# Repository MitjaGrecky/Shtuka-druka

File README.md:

# Shtuka Druka

An open, standalone desktop music instrument: synthesizer, sampler and DAW in one box.
The idea is improvising with sound from everywhere: capture audio from any source,
then shape it with filters and effects.

Status: design phase. Panel layout v7, enclosure, I/O, audio chain and compute platform are decided.
First board: M1 screen knobs module (being routed). Next: W1 Levels, then a 1:1 cardboard mockup.

## What is here

| Folder | Contents |
|---|---|
| `docs/ru/` | Research and design documents (Russian). Start with `README.md` (map of documents) and `decisions/README.md` — the single source of truth for every decision, split by topic |
| `bench/` | CPU benchmark: how many reference tracks a processor can run at 48 kHz / 128 samples |
| `mockup/` | 1:1 cardboard mockup templates (A4, PDF) and the script that generates them |
| `model3d/` | Interactive 3D model of panel v7, built from `mockup/layout/layout_v7.json` (open `index.html` in a browser; rebuild with `build_model3d_v7.py`) |
| `firmware/protocol/` | Board <-> computer protocol (SDP v0): C header for firmware and host |
| `tools/` | `sdp.py`: reference codec, self-test and frame monitor |
| `hardware/` | KiCad boards, generated from Python (`gen/`), checked by CI: `m1-screen-knobs` (first board), `w1-levels` |
| `notes/handoff.md` | Task queue between the cloud and local Claude sessions (rules in `CLAUDE.md`) |
| `.github/workflows/` | CI: ERC, DRC with schematic parity, BOM, Gerbers for every board on every push |

## Key facts

- 8x8 RGB pad grid, 16+ tracks (target 32-64), endless encoders with LED rings, 10.1" screen at 30 deg
- Body 515 x 460 mm, 68 mm high at the front, 143 mm at the rear, 30 deg slope for the screen, detachable wrist rest
- Inputs: 2 combo XLR/TRS, 2 Hi-Z, phono with RIAA, 8 line inputs, USB audio, 2-4 CV
- Converters: Cirrus Logic Pro (CS5308P/CS5304P ADC, CS4308P DAC), two-path inputs without a preamp chip
- Outputs: Main and Aux (balanced TRS), RCA copy of Main, 2 headphones
- MIDI: 2 in / 4 out DIN, 1 in / 2 out TRS (type A/B switchable); 8 CV/Gate, sync block, Ableton Link
- Compute: x86 on a Mini-ITX board (Intel N100 to start, 8-core upgrade on the same mounts)
- Two RP2350 boards (panel, control) over internal USB; audio board on two xcore.ai, USB Audio Class 2

## Licenses

- Software: GNU AGPL-3.0-or-later (`LICENSE`)
- Hardware: CERN-OHL-S-2.0 (`hardware/LICENSE`)

---

Штука Дрюка — открытый настольный инструмент: синтезатор, сэмплер и DAW в одном корпусе.
Документы проекта на русском лежат в `docs/ru/`, карта документов — `docs/ru/README.md`, все решения — в `docs/ru/decisions/` (начинать с `README.md`).

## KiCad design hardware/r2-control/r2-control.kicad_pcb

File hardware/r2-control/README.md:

# R2 - Control board (rear wall, right part)

The RP2350 of the control board (R85) with everything that is not audio at the rear wall: MIDI, CV/Gate, sync, the internal
USB hub and the control lines to the audio boards. DIN, USB, LAN and DC are panel parts on nuts with cables (R141).
Research and decisions: `docs/ru/34_rear_boards_research.md`, R118, R135-R143. Map of boards: `docs/ru/29_board_map.md`.

**Status: rev 0.6 - schematic and placed board, not routed** (234 parts, 4 layers; 14.11.2026; rev 0.5 = ATT1/ATT2 and the 74HC595, task #25; rev 0.6 = 7 x M3 mounting holes). Rear wall = the 3D model
of panel v7 (R142). MIDI DIN, USB, LAN and DC are panel parts on nuts with short cables (R141, the shelf R2b of rev 0.3 is
dropped): R2 carries the twenty 3.5 mm jacks and six JST PH headers for the DIN cables. Outline: the Control block, rear
x 88-263, z 10-113, without the window behind the DIN sockets (rear x 88-156, z 38-113) - an L, 175 x 103 mm.

| Block | Parts | Notes |
|---|---|---|
| MCU | RP2350A (C42411118), W25Q128JVSIQ (C97521, 16 MB QSPI), 12 MHz ABM8-272-T3 (C20625731), core regulator with 3.3 uH AOTA-B201610S3R3 (C42411119), BOOTSEL button | As Raspberry Pi's minimal design (Hardware design with RP2350) |
| USB hub | USB2514B (C220679), 24 MHz X322524MOB4SI (C70590) | Up: Mini-ITX USB header. Down: 1 RP2350, 2 panel P2 (R86), 3 A1 port A (R82), 4 spare. Straps low by the internal pull-downs = default configuration |
| MIDI DIN | 2 in (TLP2361 at 3.3 V), 4 out; sockets on the wall, one cable each to a JST PH header (out: 3 pins 4, 5, shield; in: 2 pins 4, 5) | CA-033 3.3 V: 33 R 0.5 W + 10 R per output; every output has its own port (R34). Any MIDI output (DIN 1-4, TRS O1/O2) can be **Thru** from In 1 or In 2, set in the menu: the RP2350 PIO copies the input bit by bit (microseconds, no CPU); no Thru labels on the panel, R144 |
| MIDI TRS | 1 in, 2 out: stereo Hroparts PJ-3920-3A (C707259, R143) | Out: tip and ring each from a GPIO through 22 R - type A/B is swapped in firmware (R32). In: two optos back to back, type A and B both work |
| CV/Gate out 1-8 | 2 x DAC80504RTET (C2862796; internal 2.5 V ref divided by 2, gain 2 = 0-2.5 V), 3 x OPA4197 (C2057327) on +-12 V | Vout = 8.06 (Vdac - 1.25 V) = -10.1 ... +10.1 V around a buffered REF/2; reset to mid-scale = 0 V; 1k output resistors. Step 0.31 mV = 0.37 cent at 1 V/oct |
| CV in 1-4 | RP2350 ADC0-3 | -10 ... +10 V -> 0 ... 3.03 V (100k / 33k to 3.3 V / 39k to GND), BAT54S clamp |
| Sync | 3 out, 2 in | Out: GPIO -> op-amp x1.51 -> 0 / +5 V. In: NPN inverter, 22k / 100k, negative clamp |
| To A1/R1 (2x7) | PH48_1, PH48_2, PHONO, MUTE, R2_OK, ATT1, ATT2 (pins 1, 3, 5, 7, 9, 11, 13; even pins GND) | Pulled low while booting; the output relays (R137) open when R2 stops; ATT1/ATT2 = -12 dB relay attenuators of Mic/Line 1-2 on R1 rev 0.3 |
| Output expander | 74HC595 (C5947) on the DAC SPI clock and data, latch GPIO 23, /OE GPIO 24 | QA PH48_1, QB PH48_2, QC PHONO, QD ATT1, QE ATT2, QF-QH spare. All 30 GPIO were in use, so the slow static lines moved here. /OE is pulled high: outputs are high-Z and the 100k pull-downs hold the lines low until the firmware loads zeros and enables them; DAC traffic only shifts the register, outputs change on the latch |

GPIO map (29 used, GPIO 25 free): 0-3 MIDI TX 1-4, 4-5 MIDI RX 1-2, 6-9 TRS out 1-2 tip/ring, 10-11 TRS in A/B, 12 MUTE,
13 R2_OK (+ status LED), 14-17 DAC SCK, SDI, CS1, CS2, 18-20 clock out 1, 2, reset/run out, 21-22 clock in, reset/run in,
23 expander latch, 24 expander /OE, 25 free, 26-29 CV in 1-4 (phantom 1-2, phono/line, ATT 1-2 on the 74HC595).

Datasheet check (rev 0.2, 14.11.2026; table in `notes/handoff.md`, report #20): RP2350 per the minimal design; DAC80504 GAIN high = x2,
RSTSEL high = mid-scale, **REFDIV high** (with the internal 2.5 V reference undivided the DAC needs VDD >= 5.0 V and raises a
reference alarm, all outputs 0 V, below that); USB2514B straps by the internal pull-downs, CRFILT/PLLFILT 100 nF, VBUS_DET 100k/100k.
Still without an LCSC number: the 0.1 % resistors (10k, 80.6k), the 1206 33 R 0.5 W, the passives in general (chosen at the BOM).

Board (`gen/make_pcb.py`): F side (jacks only) faces the rear wall; seen from behind, board x = rear x - 88, y = 113 - z.
Jacks at the model positions (axis 0.78 mm below the pad-field centre for the PJ398SM, 1.29 mm for the PJ-3920-3A). On the B side
(inside): the DIN cable headers along the window edge, power/USB/A1/SWD headers along the right edge, the ICs and the parts of
each channel packed next to their IC or jack (`hardware/common/gen/packer.py`). BOOTSEL is on the B side.
MIDI TRS: stereo **PJ-3920-3A** from JLC stock (R143) - pin 1 sleeve, 2 tip, 3 ring per the Flux library: **check the sleeve on a
sample** (tip and ring are swapped in firmware anyway, R32). Mono jacks: PJ398SM on the AudioJack2_SwitchT symbol (S, T, TN).
Panel DIN sockets at a 22 mm pitch (model): pick a panel DIN whose flange fits (e.g. round-flange types), with the enclosure.
Mounting (rev 0.6, proposal to settle with the enclosure): 7 x M3 (3.2 mm, ISO 7380 head keep-out) on standoffs to the rear wall, board
coordinates (x, y): (80, 4), (162, 4), (171, 99), (4, 99) at the corners, (23, 79) in the bottom strip between the TRS jacks, (126.5, 56) and
(92.5, 34) inside, in the 7.5 mm gaps between the jack columns and rows. The jacks' own nuts carry the plug force into the wall; the standoffs hold the
board against flexing and the cable pull of the DIN and header connectors. Before this the board had no holes at all.
Geometry without kicad-cli: `tools/pcb_geomcheck.py hardware/r2-control/r2-control.kicad_pcb` - 0 problems; pins = pads.

Checks: `tools/sch_netcheck.py hardware/r2-control` - rev 0.5 (14.11.2026, PC): 239 symbol units, 707 pins, 0 mismatches against
`design.py`; ERC by CI.

## Rear panel jacks (v3 = 3D model of panel v7, R142)

Sketch: `docs/ru/img/rear_panel_v3.png` / `.svg` (generator `tools/rear_panel.py`; v1, v2 kept). Rear view: x from the left edge as
seen from behind, z from the bottom of the 143 mm rear wall (R44). Inputs framed, outputs filled (R26); labels in English (R45).
Board "panel" = parts on nuts with a cable (R141); "R2" = on this board.

| Jack | Board | Zone | Kind | x (rear view) | z | Panel x | Direction |
|---|---|---|---|---|---|---|---|
| LAN | panel | POWER / USB | lan | 20 | 78 | 495 | io |
| USB-A | panel | POWER / USB | usba | 40 | 80 | 475 | io |
| USB-C (PC) | panel | POWER / USB | usbc | 62 | 80 | 453 | io |
| DC 12-24V | panel | POWER / USB | dc | 22 | 40 | 493 | in |
| ON/OFF | panel | POWER / USB | onoff | 52 | 40 | 463 | in |
| MIDI IN 1 | panel | CONTROL | din | 100 | 82 | 415 | in |
| MIDI OUT 1 | panel | CONTROL | din | 122 | 82 | 393 | out |
| MIDI OUT 3 | panel | CONTROL | din | 144 | 82 | 371 | out |
| MIDI IN 2 | panel | CONTROL | din | 100 | 52 | 415 | in |
| MIDI OUT 2 | panel | CONTROL | din | 122 | 52 | 393 | out |
| MIDI OUT 4 | panel | CONTROL | din | 144 | 52 | 371 | out |
| TRS IN | R2 | CONTROL | mini3 | 100 | 22 | 415 | in |
| TRS OUT 1 | R2 | CONTROL | mini3 | 122 | 22 | 393 | out |
| TRS OUT 2 | R2 | CONTROL | mini3 | 144 | 22 | 371 | out |
| CLK OUT 1 | R2 | CONTROL | mini | 172 | 90 | 343 | out |
| CLK OUT 2 | R2 | CONTROL | mini | 189 | 90 | 326 | out |
| RESET OUT | R2 | CONTROL | mini | 206 | 90 | 309 | out |
| CLK IN | R2 | CONTROL | mini | 223 | 90 | 292 | in |
| RESET IN | R2 | CONTROL | mini | 240 | 90 | 275 | in |
| CV IN 1 | R2 | CONTROL | mini | 172 | 68 | 343 | in |
| CV IN 2 | R2 | CONTROL | mini | 189 | 68 | 326 | in |
| CV IN 3 | R2 | CONTROL | mini | 206 | 68 | 309 | in |
| CV IN 4 | R2 | CONTROL | mini | 223 | 68 | 292 | in |
| CV OUT 1 | R2 | CONTROL | mini | 172 | 46 | 343 | out |
| CV OUT 2 | R2 | CONTROL | mini | 189 | 46 | 326 | out |
| CV OUT 3 | R2 | CONTROL | mini | 206 | 46 | 309 | out |
| CV OUT 4 | R2 | CONTROL | mini | 223 | 46 | 292 | out |
| CV OUT 5 | R2 | CONTROL | mini | 172 | 24 | 343 | out |
| CV OUT 6 | R2 | CONTROL | mini | 189 | 24 | 326 | out |
| CV OUT 7 | R2 | CONTROL | mini | 206 | 24 | 309 | out |
| CV OUT 8 | R2 | CONTROL | mini | 223 | 24 | 292 | out |

Generators: `gen/design.py`, `gen/make_sch.py` (shared writer `hardware/common/gen/module_sch.py`, multi-unit symbols placed unit by unit).

License: CERN-OHL-S-2.0 (hardware), AGPL-3.0-or-later (scripts).

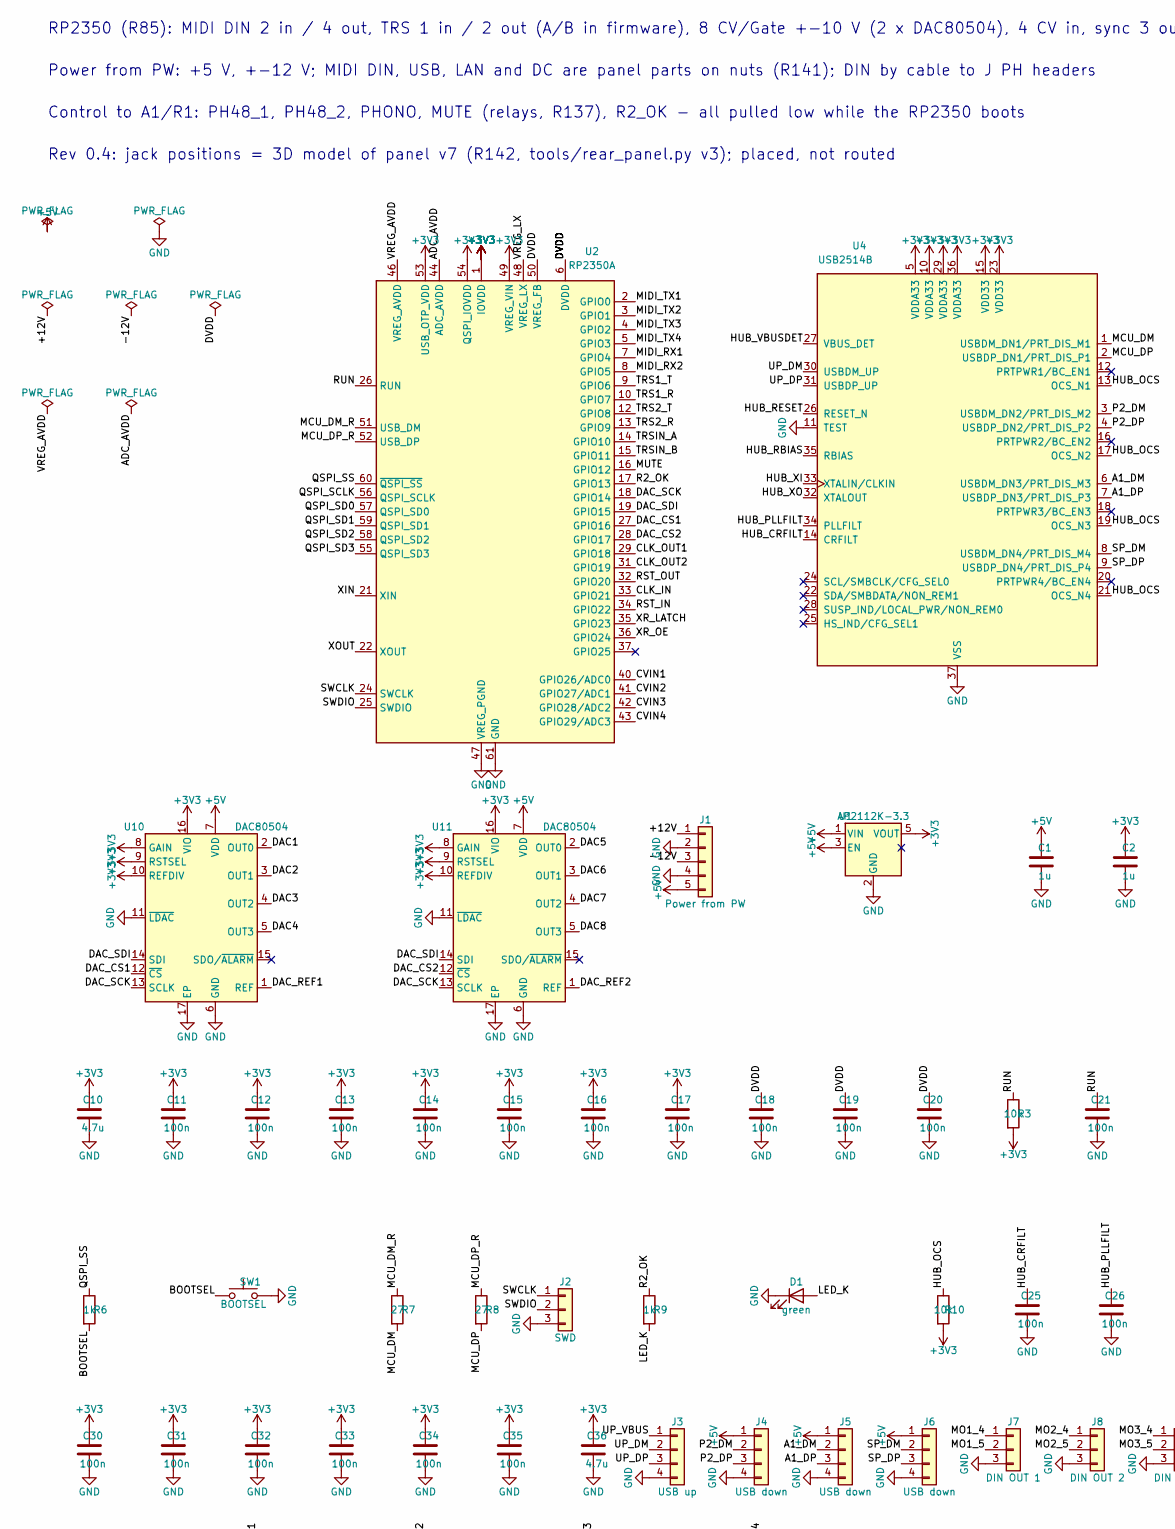
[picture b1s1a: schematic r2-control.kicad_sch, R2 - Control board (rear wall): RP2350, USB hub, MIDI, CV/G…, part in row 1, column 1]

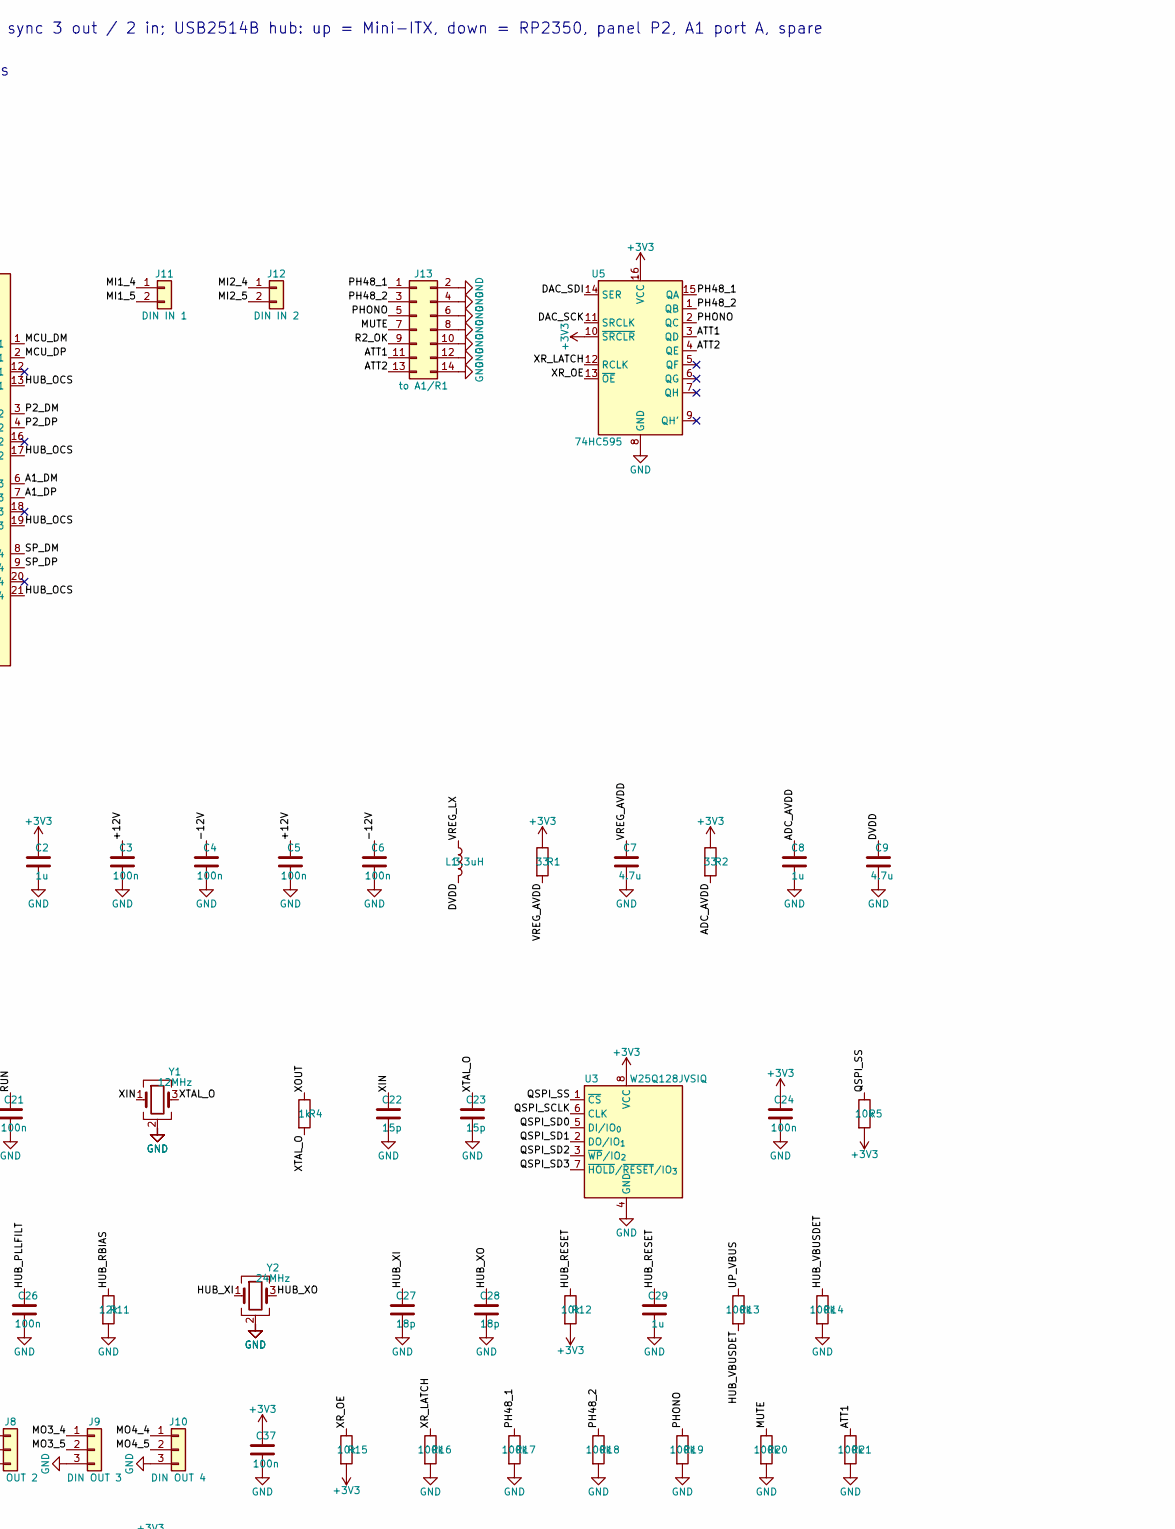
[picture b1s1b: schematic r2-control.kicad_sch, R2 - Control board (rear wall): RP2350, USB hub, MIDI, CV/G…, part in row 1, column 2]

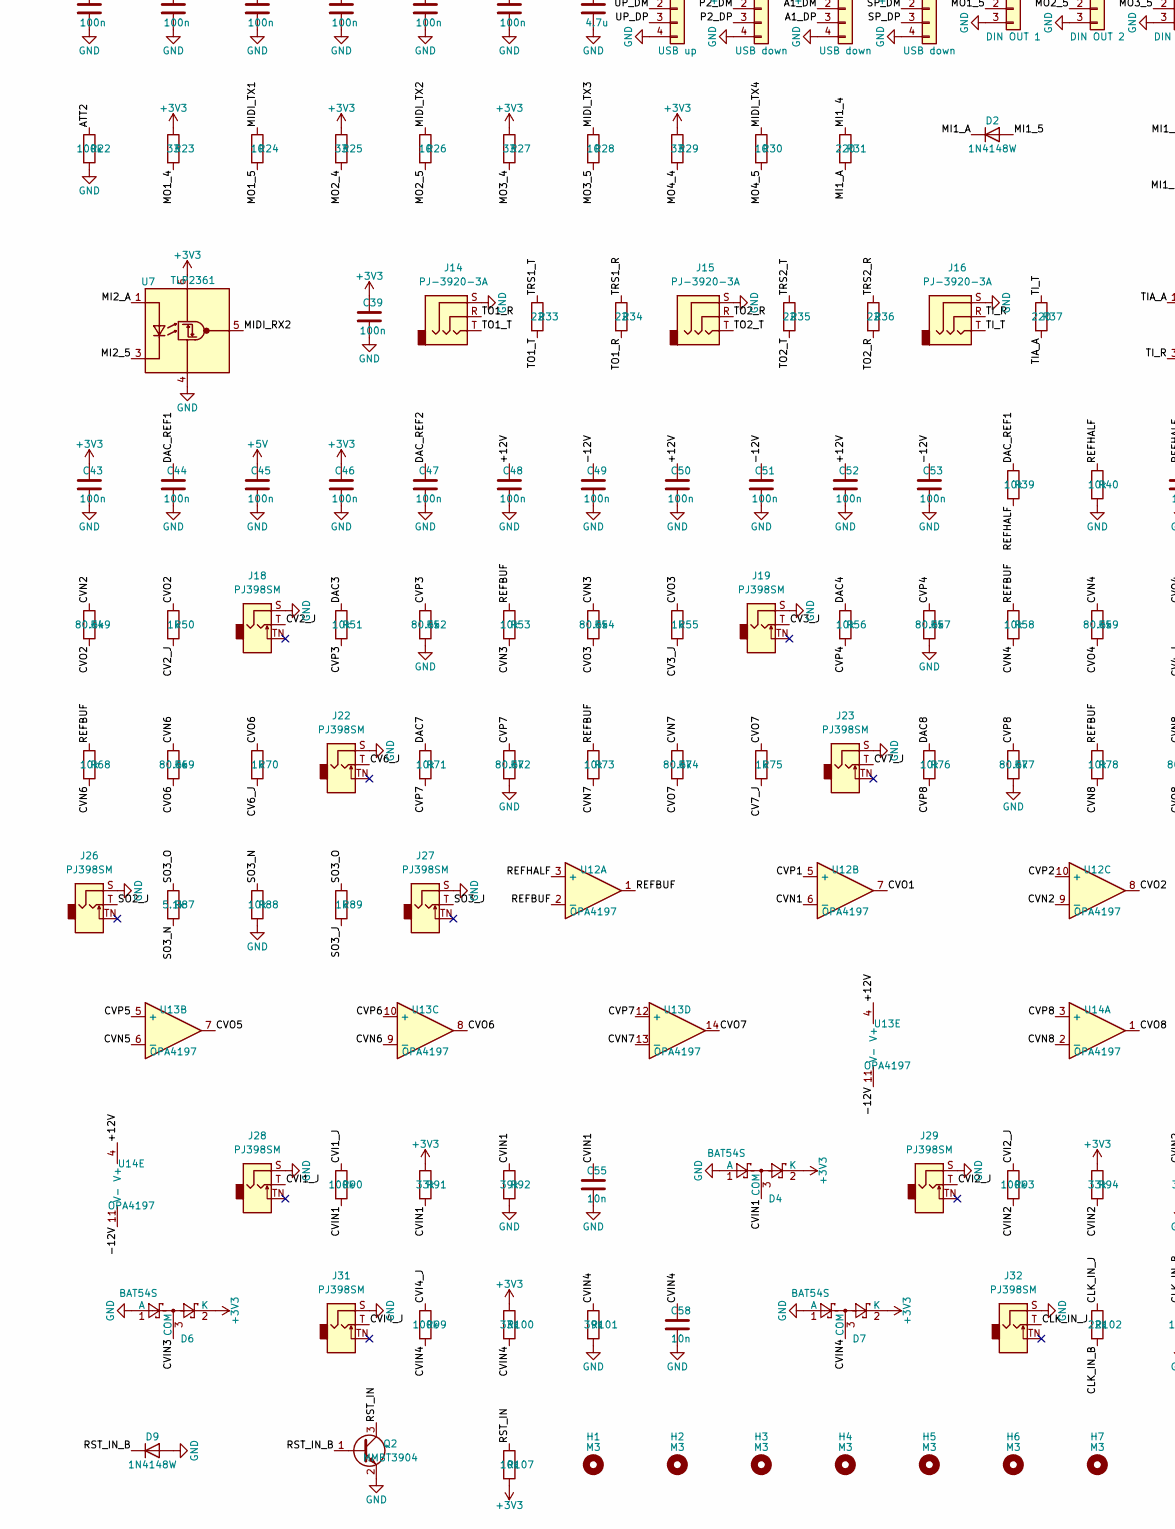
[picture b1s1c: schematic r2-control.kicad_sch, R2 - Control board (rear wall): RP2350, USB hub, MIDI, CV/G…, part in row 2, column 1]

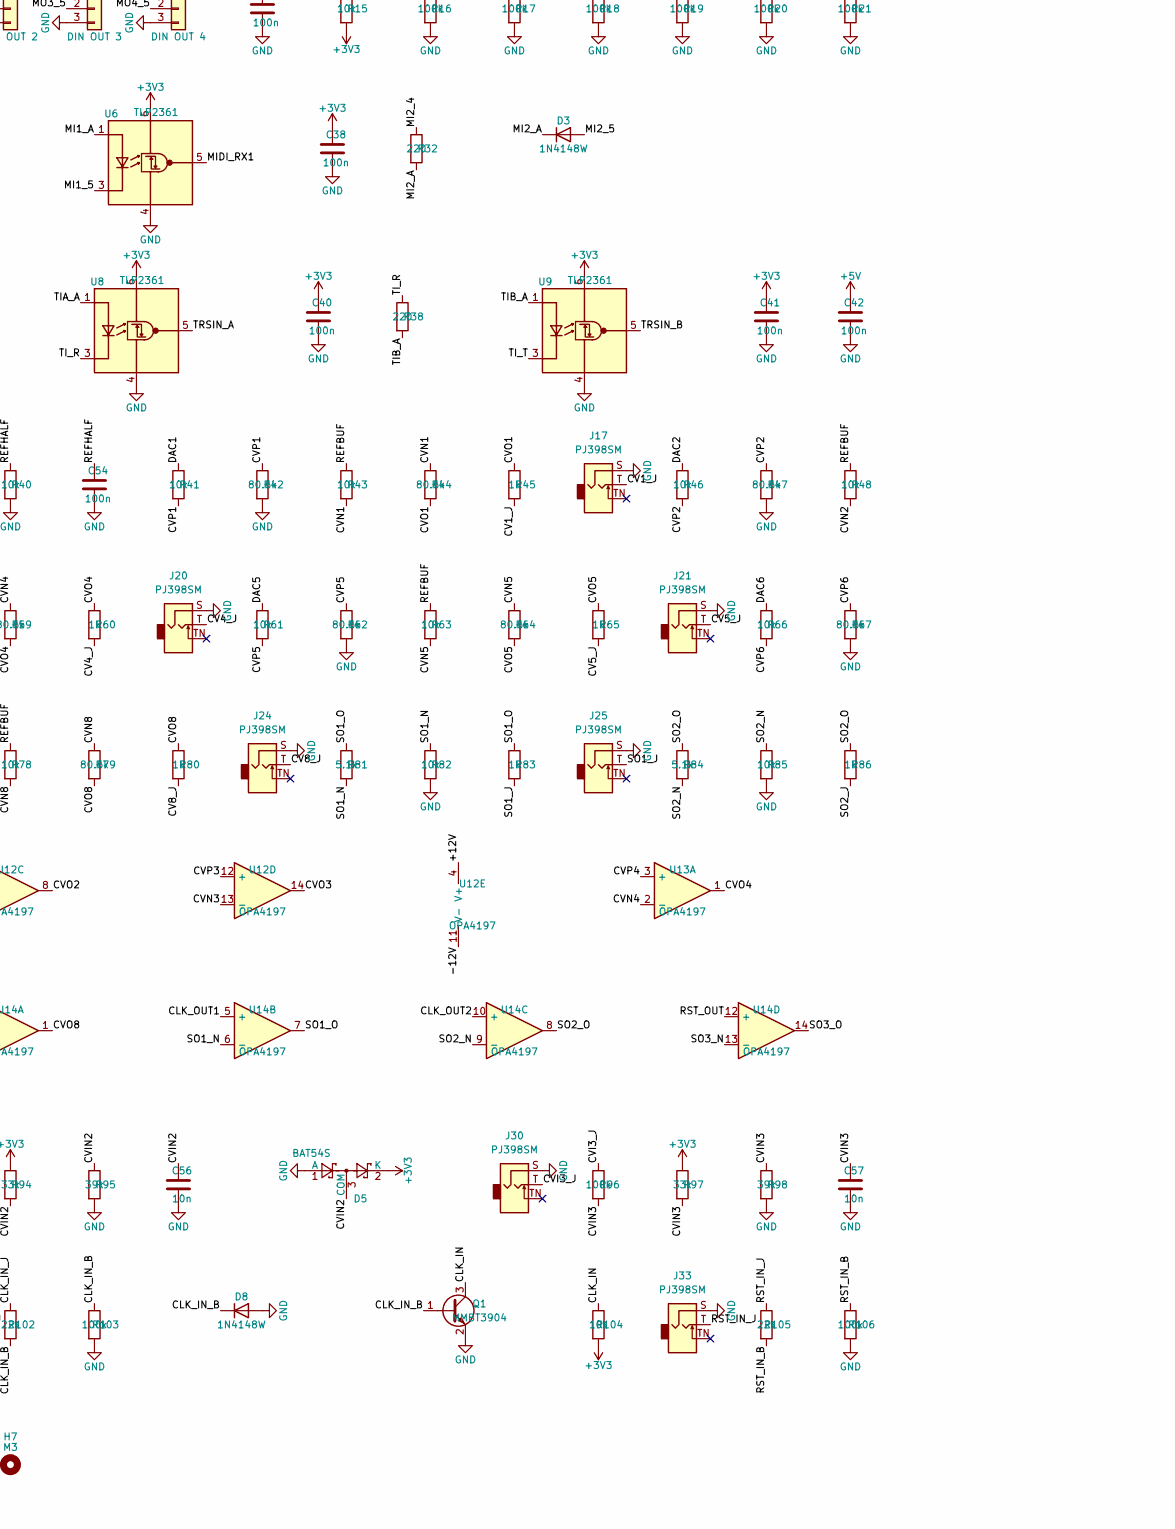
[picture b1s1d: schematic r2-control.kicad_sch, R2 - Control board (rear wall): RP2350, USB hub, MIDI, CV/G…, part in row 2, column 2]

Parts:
C1, C2, C8, C29: 1u; C_0402_1005Metric; LCSC C52923
C3, C4, C5, C6, C11, C12, C13, C14, C15, C16, C17, C18, C19, C20, C21, C24, C25, C26, C30, C31, C32, C33, C34, C35, C37, C38, C39, C40, C41, C42, C43, C44, C45, C46, C47, C48, C49, C50, C51, C52, C53, C54: 100n; C_0402_1005Metric; LCSC C1525
C7, C9, C10, C36: 4.7u; C_0805_2012Metric; LCSC C1779
C22, C23: 15p; C_0402_1005Metric
C27, C28: 18p; C_0402_1005Metric
C55, C56, C57, C58: 10n; C_0402_1005Metric
D1: green; LED_0603_1608Metric
D2, D3, D8, D9: 1N4148W; D_SOD-123
D4, D5, D6, D7: BAT54S; SOT-23
H1, H2, H3, H4, H5, H6, H7: M3; MountingHole_3.2mm_M3_ISO7380
J1: Power from PW; JST_PH_B5B-PH-K_1x05_P2.00mm_Vertical
J2: SWD; JST_PH_B3B-PH-K_1x03_P2.00mm_Vertical
J3: USB up; JST_PH_B4B-PH-K_1x04_P2.00mm_Vertical
J4, J5, J6: USB down; JST_PH_B4B-PH-K_1x04_P2.00mm_Vertical
J7: DIN OUT 1; JST_PH_B3B-PH-K_1x03_P2.00mm_Vertical
J8: DIN OUT 2; JST_PH_B3B-PH-K_1x03_P2.00mm_Vertical
J9: DIN OUT 3; JST_PH_B3B-PH-K_1x03_P2.00mm_Vertical
J10: DIN OUT 4; JST_PH_B3B-PH-K_1x03_P2.00mm_Vertical
J11: DIN IN 1; JST_PH_B2B-PH-K_1x02_P2.00mm_Vertical
J12: DIN IN 2; JST_PH_B2B-PH-K_1x02_P2.00mm_Vertical
J13: to A1/R1; PinHeader_2x07_P2.54mm_Vertical
J14, J15, J16: PJ-3920-3A; Jack_3.5mm_Hroparts_PJ-3920-3A_Vertical; LCSC C707259
J17, J18, J19, J20, J21, J22, J23, J24, J25, J26, J27, J28, J29, J30, J31, J32, J33: PJ398SM; Jack_3.5mm_QingPu_WQP-PJ398SM_Vertical_CircularHoles; LCSC C9900009788
L1: 3.3uH; L_Abracon_AOTA-B201610S; LCSC C42411119
Q1, Q2: MMBT3904; SOT-23
R1, R2: 33; R_0402_1005Metric
R3, R5, R10, R12, R15, R39, R40, R41, R43, R46, R48, R51, R53, R56, R58, R61, R63, R66, R68, R71, R73, R76, R78, R82, R85, R88, R104, R107: 10k; R_0402_1005Metric; LCSC C25744
R4, R6, R9, R45, R50, R55, R60, R65, R70, R75, R80, R83, R86, R89: 1k; R_0402_1005Metric; LCSC C11702
R7, R8: 27; R_0402_1005Metric
R11: 12k; R_0402_1005Metric
R13, R14, R16, R17, R18, R19, R20, R21, R22, R90, R93, R96, R99, R103, R106: 100k; R_0402_1005Metric
R23, R25, R27, R29: 33; R_1206_3216Metric
R24, R26, R28, R30: 10; R_0402_1005Metric
R31, R32, R37, R38: 220; R_0402_1005Metric
R33, R34, R35, R36: 22; R_0402_1005Metric
R42, R44, R47, R49, R52, R54, R57, R59, R62, R64, R67, R69, R72, R74, R77, R79: 80.6k; R_0402_1005Metric
R81, R84, R87: 5.1k; R_0402_1005Metric
R91, R94, R97, R100: 33k; R_0402_1005Metric
R92, R95, R98, R101: 39k; R_0402_1005Metric
R102, R105: 22k; R_0402_1005Metric
SW1: BOOTSEL; SW_Push_1P1T_XKB_TS-1187A; LCSC C318884
U1: AP2112K-3.3; SOT-23-5; LCSC C51118
U2: RP2350A; QFN-60-1EP_7x7mm_P0.4mm_EP3.4x3.4mm; LCSC C42411118
U3: W25Q128JVSIQ; SOIC-8_5.3x5.3mm_P1.27mm; LCSC C97521
U4: USB2514B; QFN-36-1EP_6x6mm_P0.5mm_EP3.7x3.7mm; LCSC C220679
U5: 74HC595; SOIC-16_3.9x9.9mm_P1.27mm; LCSC C5947
U6, U7, U8, U9: TLP2361; SO-5-6_4.55x3.7mm_P1.27mm; LCSC C107626
U10, U11: DAC80504; Texas_RTE0016D_WQFN-16-1EP_3x3mm_P0.5mm_EP0.8x0.8mm_Thermal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; LCSC C2862796
U12, U13, U14: OPA4197; TSSOP-14_4.4x5mm_P0.65mm; LCSC C2057327
Y1: 12MHz; Crystal_SMD_3225-4Pin_3.2x2.5mm; LCSC C20625731
Y2: 24MHz; Crystal_SMD_3225-4Pin_3.2x2.5mm; LCSC C70590

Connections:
+3V3: C2.1, C10.1, C11.1, C12.1, C13.1, C14.1, C15.1, C16.1, C17.1, C24.1, C30.1, C31.1, C32.1, C33.1, C34.1, C35.1, C36.1, C37.1, C38.1, C39.1, C40.1, C41.1, C43.1, C46.1, D4.2 (K), D5.2 (K), D6.2 (K), D7.2 (K), R1.1, R2.1, R3.2, R5.2, R10.2, R12.2, R15.2, R23.1, R25.1, R27.1, R29.1, R91.1, R94.1, R97.1, R100.1, R104.2, R107.2, U1.5 (VOUT), U2.1 (IOVDD), U2.11 (IOVDD), U2.20 (IOVDD), U2.30 (IOVDD), U2.38 (IOVDD), U2.45 (IOVDD), U2.49 (VREG_VIN), U2.53 (USB_OTP_VDD), U2.54 (QSPI_IOVDD), U3.8 (VCC), U4.5 (VDDA33), U4.10 (VDDA33), U4.15 (VDD33), U4.23 (VDD33), U4.29 (VDDA33), U4.36 (VDDA33), U5.10 (~SRCLR), U5.16 (VCC), U6.6 (VDD), U7.6 (VDD), U8.6 (VDD), U9.6 (VDD), U10.8 (GAIN), U10.9 (RSTSEL), U10.10 (REFDIV), U10.16 (VIO), U11.8 (GAIN), U11.9 (RSTSEL), U11.10 (REFDIV), U11.16 (VIO)
+5V: C1.1, C42.1, C45.1, J1.5, J4.1, J5.1, J6.1, U1.1 (VIN), U1.3 (EN), U10.7 (VDD), U11.7 (VDD)
/+12V: C3.1, C5.1, C48.1, C50.1, C52.1, J1.1, U12.4 (V+), U13.4 (V+), U14.4 (V+)
/-12V: C4.1, C6.1, C49.1, C51.1, C53.1, J1.3, U12.11 (V-), U13.11 (V-), U14.11 (V-)
/A1_DM: J5.2, U4.6 (USBDM_DN3/PRT_DIS_M3)
/A1_DP: J5.3, U4.7 (USBDP_DN3/PRT_DIS_P3)
/ADC_AVDD: C8.1, R2.2, U2.44 (ADC_AVDD)
/ATT1: J13.11, R21.1, U5.3 (QD)
/ATT2: J13.13, R22.1, U5.4 (QE)
/BOOTSEL: R6.2, SW1.1
/CLK_IN: Q1.3 (C), R104.1, U2.33 (GPIO21)
/CLK_IN_B: D8.1 (K), Q1.1 (B), R102.2, R103.1
/CLK_IN_J: J32.T, R102.1
/CLK_OUT1: U2.29 (GPIO18), U14.5 (+)
/CLK_OUT2: U2.31 (GPIO19), U14.10 (+)
/CV1_J: J17.T, R45.2
/CV2_J: J18.T, R50.2
/CV3_J: J19.T, R55.2
/CV4_J: J20.T, R60.2
/CV5_J: J21.T, R65.2
/CV6_J: J22.T, R70.2
/CV7_J: J23.T, R75.2
/CV8_J: J24.T, R80.2
/CVI1_J: J28.T, R90.1
/CVI2_J: J29.T, R93.1
/CVI3_J: J30.T, R96.1
/CVI4_J: J31.T, R99.1
/CVIN1: C55.1, D4.3 (COM), R90.2, R91.2, R92.1, U2.40 (GPIO26/ADC0)
/CVIN2: C56.1, D5.3 (COM), R93.2, R94.2, R95.1, U2.41 (GPIO27/ADC1)
/CVIN3: C57.1, D6.3 (COM), R96.2, R97.2, R98.1, U2.42 (GPIO28/ADC2)
/CVIN4: C58.1, D7.3 (COM), R99.2, R100.2, R101.1, U2.43 (GPIO29/ADC3)
/CVN1: R43.2, R44.1, U12.6 (-)
/CVN2: R48.2, R49.1, U12.9 (-)
/CVN3: R53.2, R54.1, U12.13 (-)
/CVN4: R58.2, R59.1, U13.2 (-)
/CVN5: R63.2, R64.1, U13.6 (-)
/CVN6: R68.2, R69.1, U13.9 (-)
/CVN7: R73.2, R74.1, U13.13 (-)
/CVN8: R78.2, R79.1, U14.2 (-)
/CVO1: R44.2, R45.1, U12.7
/CVO2: R49.2, R50.1, U12.8
/CVO3: R54.2, R55.1, U12.14
/CVO4: R59.2, R60.1, U13.1
/CVO5: R64.2, R65.1, U13.7
/CVO6: R69.2, R70.1, U13.8
/CVO7: R74.2, R75.1, U13.14
/CVO8: R79.2, R80.1, U14.1
/CVP1: R41.2, R42.1, U12.5 (+)
/CVP2: R46.2, R47.1, U12.10 (+)
/CVP3: R51.2, R52.1, U12.12 (+)
/CVP4: R56.2, R57.1, U13.3 (+)
/CVP5: R61.2, R62.1, U13.5 (+)
/CVP6: R66.2, R67.1, U13.10 (+)
/CVP7: R71.2, R72.1, U13.12 (+)
/CVP8: R76.2, R77.1, U14.3 (+)
/DAC1: R41.1, U10.2 (OUT0)
/DAC2: R46.1, U10.3 (OUT1)
/DAC3: R51.1, U10.4 (OUT2)
/DAC4: R56.1, U10.5 (OUT3)
/DAC5: R61.1, U11.2 (OUT0)
/DAC6: R66.1, U11.3 (OUT1)
/DAC7: R71.1, U11.4 (OUT2)
/DAC8: R76.1, U11.5 (OUT3)
/DAC_CS1: U2.27 (GPIO16), U10.12 (~CS)
/DAC_CS2: U2.28 (GPIO17), U11.12 (~CS)
/DAC_REF1: C44.1, R39.1, U10.1 (REF)
/DAC_REF2: C47.1, U11.1 (REF)
/DAC_SCK: U2.18 (GPIO14), U5.11 (SRCLK), U10.13 (SCLK), U11.13 (SCLK)
/DAC_SDI: U2.19 (GPIO15), U5.14 (SER), U10.14 (SDI), U11.14 (SDI)
/DVDD: C9.1, C18.1, C19.1, C20.1, L1.2, U2.6 (DVDD), U2.23 (DVDD), U2.39 (DVDD), U2.50 (VREG_FB)
/HUB_CRFILT: C25.1, U4.14 (CRFILT)
/HUB_OCS: R10.1, U4.13 (OCS_N1), U4.17 (OCS_N2), U4.19 (OCS_N3), U4.21 (OCS_N4)
/HUB_PLLFILT: C26.1, U4.34 (PLLFILT)
/HUB_RBIAS: R11.1, U4.35 (RBIAS)
/HUB_RESET: C29.1, R12.1, U4.26 (RESET_N)
/HUB_VBUSDET: R13.2, R14.1, U4.27 (VBUS_DET)
/HUB_XI: C27.1, U4.33 (XTALIN/CLKIN), Y2.1
/HUB_XO: C28.1, U4.32 (XTALOUT), Y2.3
/LED_K: D1.2 (A), R9.2
/MCU_DM: R7.2, U4.1 (USBDM_DN1/PRT_DIS_M1)
/MCU_DM_R: R7.1, U2.51 (USB_DM)
/MCU_DP: R8.2, U4.2 (USBDP_DN1/PRT_DIS_P1)
/MCU_DP_R: R8.1, U2.52 (USB_DP)
/MI1_4: J11.1, R31.1
/MI1_5: D2.2 (A), J11.2, U6.3 (K)
/MI1_A: D2.1 (K), R31.2, U6.1 (A)
/MI2_4: J12.1, R32.1
/MI2_5: D3.2 (A), J12.2, U7.3 (K)
/MI2_A: D3.1 (K), R32.2, U7.1 (A)
/MIDI_RX1: U2.7 (GPIO4), U6.5 (VO)
/MIDI_RX2: U2.8 (GPIO5), U7.5 (VO)
/MIDI_TX1: R24.1, U2.2 (GPIO0)
/MIDI_TX2: R26.1, U2.3 (GPIO1)
/MIDI_TX3: R28.1, U2.4 (GPIO2)
/MIDI_TX4: R30.1, U2.5 (GPIO3)
/MO1_4: J7.1, R23.2
/MO1_5: J7.2, R24.2
/MO2_4: J8.1, R25.2
/MO2_5: J8.2, R26.2
/MO3_4: J9.1, R27.2
/MO3_5: J9.2, R28.2
/MO4_4: J10.1, R29.2
/MO4_5: J10.2, R30.2
/MUTE: J13.7, R20.1, U2.16 (GPIO12)
/P2_DM: J4.2, U4.3 (USBDM_DN2/PRT_DIS_M2)
/P2_DP: J4.3, U4.4 (USBDP_DN2/PRT_DIS_P2)
/PH48_1: J13.1, R17.1, U5.15 (QA)
/PH48_2: J13.3, R18.1, U5.1 (QB)
/PHONO: J13.5, R19.1, U5.2 (QC)
/QSPI_SCLK: U2.56 (QSPI_SCLK), U3.6 (CLK)
/QSPI_SD0: U2.57 (QSPI_SD0), U3.5 (DI/IO_{0})
/QSPI_SD1: U2.59 (QSPI_SD1), U3.2 (DO/IO_{1})
/QSPI_SD2: U2.58 (QSPI_SD2), U3.3 (~WP/IO_{2})
/QSPI_SD3: U2.55 (QSPI_SD3), U3.7 (~HOLD/~RESET/IO_{3})
/QSPI_SS: R5.1, R6.1, U2.60 (~QSPI_SS), U3.1 (~CS)
/R2_OK: J13.9, R9.1, U2.17 (GPIO13)
/REFBUF: R43.1, R48.1, R53.1, R58.1, R63.1, R68.1, R73.1, R78.1, U12.1, U12.2 (-)
/REFHALF: C54.1, R39.2, R40.1, U12.3 (+)
/RST_IN: Q2.3 (C), R107.1, U2.34 (GPIO22)
/RST_IN_B: D9.1 (K), Q2.1 (B), R105.2, R106.1
/RST_IN_J: J33.T, R105.1
/RST_OUT: U2.32 (GPIO20), U14.12 (+)
/RUN: C21.1, R3.1, U2.26 (RUN)
/SO1_J: J25.T, R83.2
/SO1_N: R81.2, R82.1, U14.6 (-)
/SO1_O: R81.1, R83.1, U14.7
/SO2_J: J26.T, R86.2
/SO2_N: R84.2, R85.1, U14.9 (-)
/SO2_O: R84.1, R86.1, U14.8
/SO3_J: J27.T, R89.2
/SO3_N: R87.2, R88.1, U14.13 (-)
/SO3_O: R87.1, R89.1, U14.14
/SP_DM: J6.2, U4.8 (USBDM_DN4/PRT_DIS_M4)
/SP_DP: J6.3, U4.9 (USBDP_DN4/PRT_DIS_P4)
/SWCLK: J2.1, U2.24 (SWCLK)
/SWDIO: J2.2, U2.25 (SWDIO)
/TIA_A: R37.2, U8.1 (A)
/TIB_A: R38.2, U9.1 (A)
/TI_R: J16.R, R38.1, U8.3 (K)
/TI_T: J16.T, R37.1, U9.3 (K)
/TO1_R: J14.R, R34.2
/TO1_T: J14.T, R33.2
/TO2_R: J15.R, R36.2
/TO2_T: J15.T, R35.2
/TRS1_R: R34.1, U2.10 (GPIO7)
/TRS1_T: R33.1, U2.9 (GPIO6)
/TRS2_R: R36.1, U2.13 (GPIO9)
/TRS2_T: R35.1, U2.12 (GPIO8)
/TRSIN_A: U2.14 (GPIO10), U8.5 (VO)
/TRSIN_B: U2.15 (GPIO11), U9.5 (VO)
/UP_DM: J3.2, U4.30 (USBDM_UP)
/UP_DP: J3.3, U4.31 (USBDP_UP)
/UP_VBUS: J3.1, R13.1
/VREG_AVDD: C7.1, R1.2, U2.46 (VREG_AVDD)
/VREG_LX: L1.1, U2.48 (VREG_LX)
/XIN: C22.1, U2.21 (XIN), Y1.1
/XOUT: R4.1, U2.22 (XOUT)
/XR_LATCH: R16.1, U2.35 (GPIO23), U5.12 (RCLK)
/XR_OE: R15.1, U2.36 (GPIO24), U5.13 (~OE)
/XTAL_O: C23.1, R4.2, Y1.3
GND: C1.2, C2.2, C3.2, C4.2, C5.2, C6.2, C7.2, C8.2, C9.2, C10.2, C11.2, C12.2, C13.2, C14.2, C15.2, C16.2, C17.2, C18.2, C19.2, C20.2, C21.2, C22.2, C23.2, C24.2, C25.2, C26.2, C27.2, C28.2, C29.2, C30.2, C31.2, C32.2, C33.2, C34.2, C35.2, C36.2, C37.2, C38.2, C39.2, C40.2, C41.2, C42.2, C43.2, C44.2, C45.2, C46.2, C47.2, C48.2, C49.2, C50.2, C51.2, C52.2, C53.2, C54.2, C55.2, C56.2, C57.2, C58.2, D1.1 (K), D4.1 (A), D5.1 (A), D6.1 (A), D7.1 (A), D8.2 (A), D9.2 (A), J1.2, J1.4, J2.3, J3.4, J4.4, J5.4, J6.4, J7.3, J8.3, J9.3, J10.3, J13.2, J13.4, J13.6, J13.8, J13.10, J13.12, J13.14, J14.S, J15.S, J16.S, J17.S, J18.S, J19.S, J20.S, J21.S, J22.S, J23.S, J24.S, J25.S, J26.S, J27.S, J28.S, J29.S, J30.S, J31.S, J32.S, J33.S, Q1.2 (E), Q2.2 (E), R11.2, R14.2, R16.2, R17.2, R18.2, R19.2, R20.2, R21.2, R22.2, R40.2, R42.2, R47.2, R52.2, R57.2, R62.2, R67.2, R72.2, R77.2, R82.2, R85.2, R88.2, R92.2, R95.2, R98.2, R101.2, R103.2, R106.2, SW1.2, U1.2 (GND), U2.47 (VREG_PGND), U2.61 (GND), U3.4 (GND), U4.11 (TEST), U4.37 (VSS), U5.8 (GND), U6.4 (GND), U7.4 (GND), U8.4 (GND), U9.4 (GND), U10.6 (GND), U10.11 (~LDAC), U10.17 (EP), U11.6 (GND), U11.11 (~LDAC), U11.17 (EP), Y1.2 (G), Y1.4 (G), Y2.2 (G), Y2.4 (G)

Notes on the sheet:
RP2350 (R85): MIDI DIN 2 in / 4 out, TRS 1 in / 2 out (A/B in firmware), 8 CV/Gate +-10 V (2 x DAC80504), 4 CV in, sync 3 out / 2 in; USB2514B hub: up = Mini-ITX, down = RP2350, panel P2, A1 port A, spare
Power from PW: +5 V, +-12 V; MIDI DIN, USB, LAN and DC are panel parts on nuts (R141); DIN by cable to J PH headers
Control to A1/R1: PH48_1, PH48_2, PHONO, MUTE (relays, R137), R2_OK - all pulled low while the RP2350 boots
Rev 0.4: jack positions = 3D model of panel v7 (R142, tools/rear_panel.py v3); placed, not routed

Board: 4 copper layers, 234 parts (207 on the bottom side), 161 nets, no tracks yet.

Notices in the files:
hardware/m1-screen-knobs/almost/m1-screen-knobs.kicad_sch:
Shtuka Druka - open hardware, CERN-OHL-S-2.0
hardware/m1-screen-knobs/m1-screen-knobs.kicad_pcb:
M1 rev 0.5  CERN-OHL-S-2.0
hardware/m5-gain/m5-gain.kicad_pcb:
Shtuka Druka CERN-OHL-S-2.0
